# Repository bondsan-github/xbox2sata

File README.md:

Aim
===
- Create a IDE to SATA bridge PCB with pass-through socket for XBox DVD cable.
- !3d render[3d render](/Images/3d_render.png)

Motivation
==========
- Remove the need for a 80 wire IDE cable
- Use existing IDE cable for DVD drive

Completed
=========
- Unverified schematic of Startech IDE2SATA pcb
- Startech IDE2SATA layer scans and annotations in GIMP .xcf image format.

To do
=====
Measure components;
- L1

- Find suitable 3V3 and ground points to tap on XBox motherboards
- Measure available space inside XBox under DVD drive.
  - there is/are a radial capacaitor/s close to the IDE header
    - I would like to not make a hole in the PCB for matched IDE to IDE routing lengths
    - The capactor/s have enough leg legnth to pull up and lay flat

- Can xbox ide connection be directly connected to DVD connection?
  - Simular how a IDE cable does?
  - IDE cable does have CSEL tied hi or low depending on device?
- Can LED circuit be removed? Is it for HDD activity?
- CSEL cable selection can be fixed as DVD will always be device 0 (slave) and SATA device 1 (master)?
- What capacitors are required for power input from xbox motherboard?

Requirements
============
- Marvell 88SA8052 - NNC2 IC
  -  PATA/ATAPI to SATA bridge chip W/ATAPI, 3 GBps SATA
     -  64 pin
     -  package: PQFN50P900X900X90-65
  - 1V2 Voltage regulator for Marvel IC Vdd
  - 3V3 for Marvel Vddio 
  - 25Mhz crystal oscillator
  - CNFG0,1,2 setup
  - T0,1,2,3,4,5,6,7,8 setup
  - will require 3V3 and ground solder points from all six motherboard revisions
    - 1.0 , 1.1 , 1.2 , 1.3 , 1.4 , 1.6/b

- xbox motherboard IDE socket
- DVD drive IDE header
- SATA to HDD/SATA socket

Desirables
==========
- Marvell 88SA8052 datasheet
- Connect pcb directly to xbox ide header on motherboard.
- Use motherboard 3V3 reducing one power regulator.
- Use existing IDE cable from pcb to dvd drive.
  - Cut or roll second connector behind dvd drive.
- Use power from existing molex connector to HDD/SSD.
  
Software used
=============
- GIMP 2.99.18 development release
- KiCad Schematic Editor 8.0.1
- Proteus 8.15 SP1
  
Sources
=======
- https://www.psdevwiki.com/ps3/88SA8040-TBC1
- https://consolemods.org/wiki/Xbox:Versions
- https://www.ioi.com.tw/products/proddetail.aspx?CatID=101&HostID=2010&DeviceID=3002&ProdID=1010114
- https://en.wikipedia.org/wiki/Parallel_ATA
- https://www.startech.com/en-gb/hdd/ide2sat2

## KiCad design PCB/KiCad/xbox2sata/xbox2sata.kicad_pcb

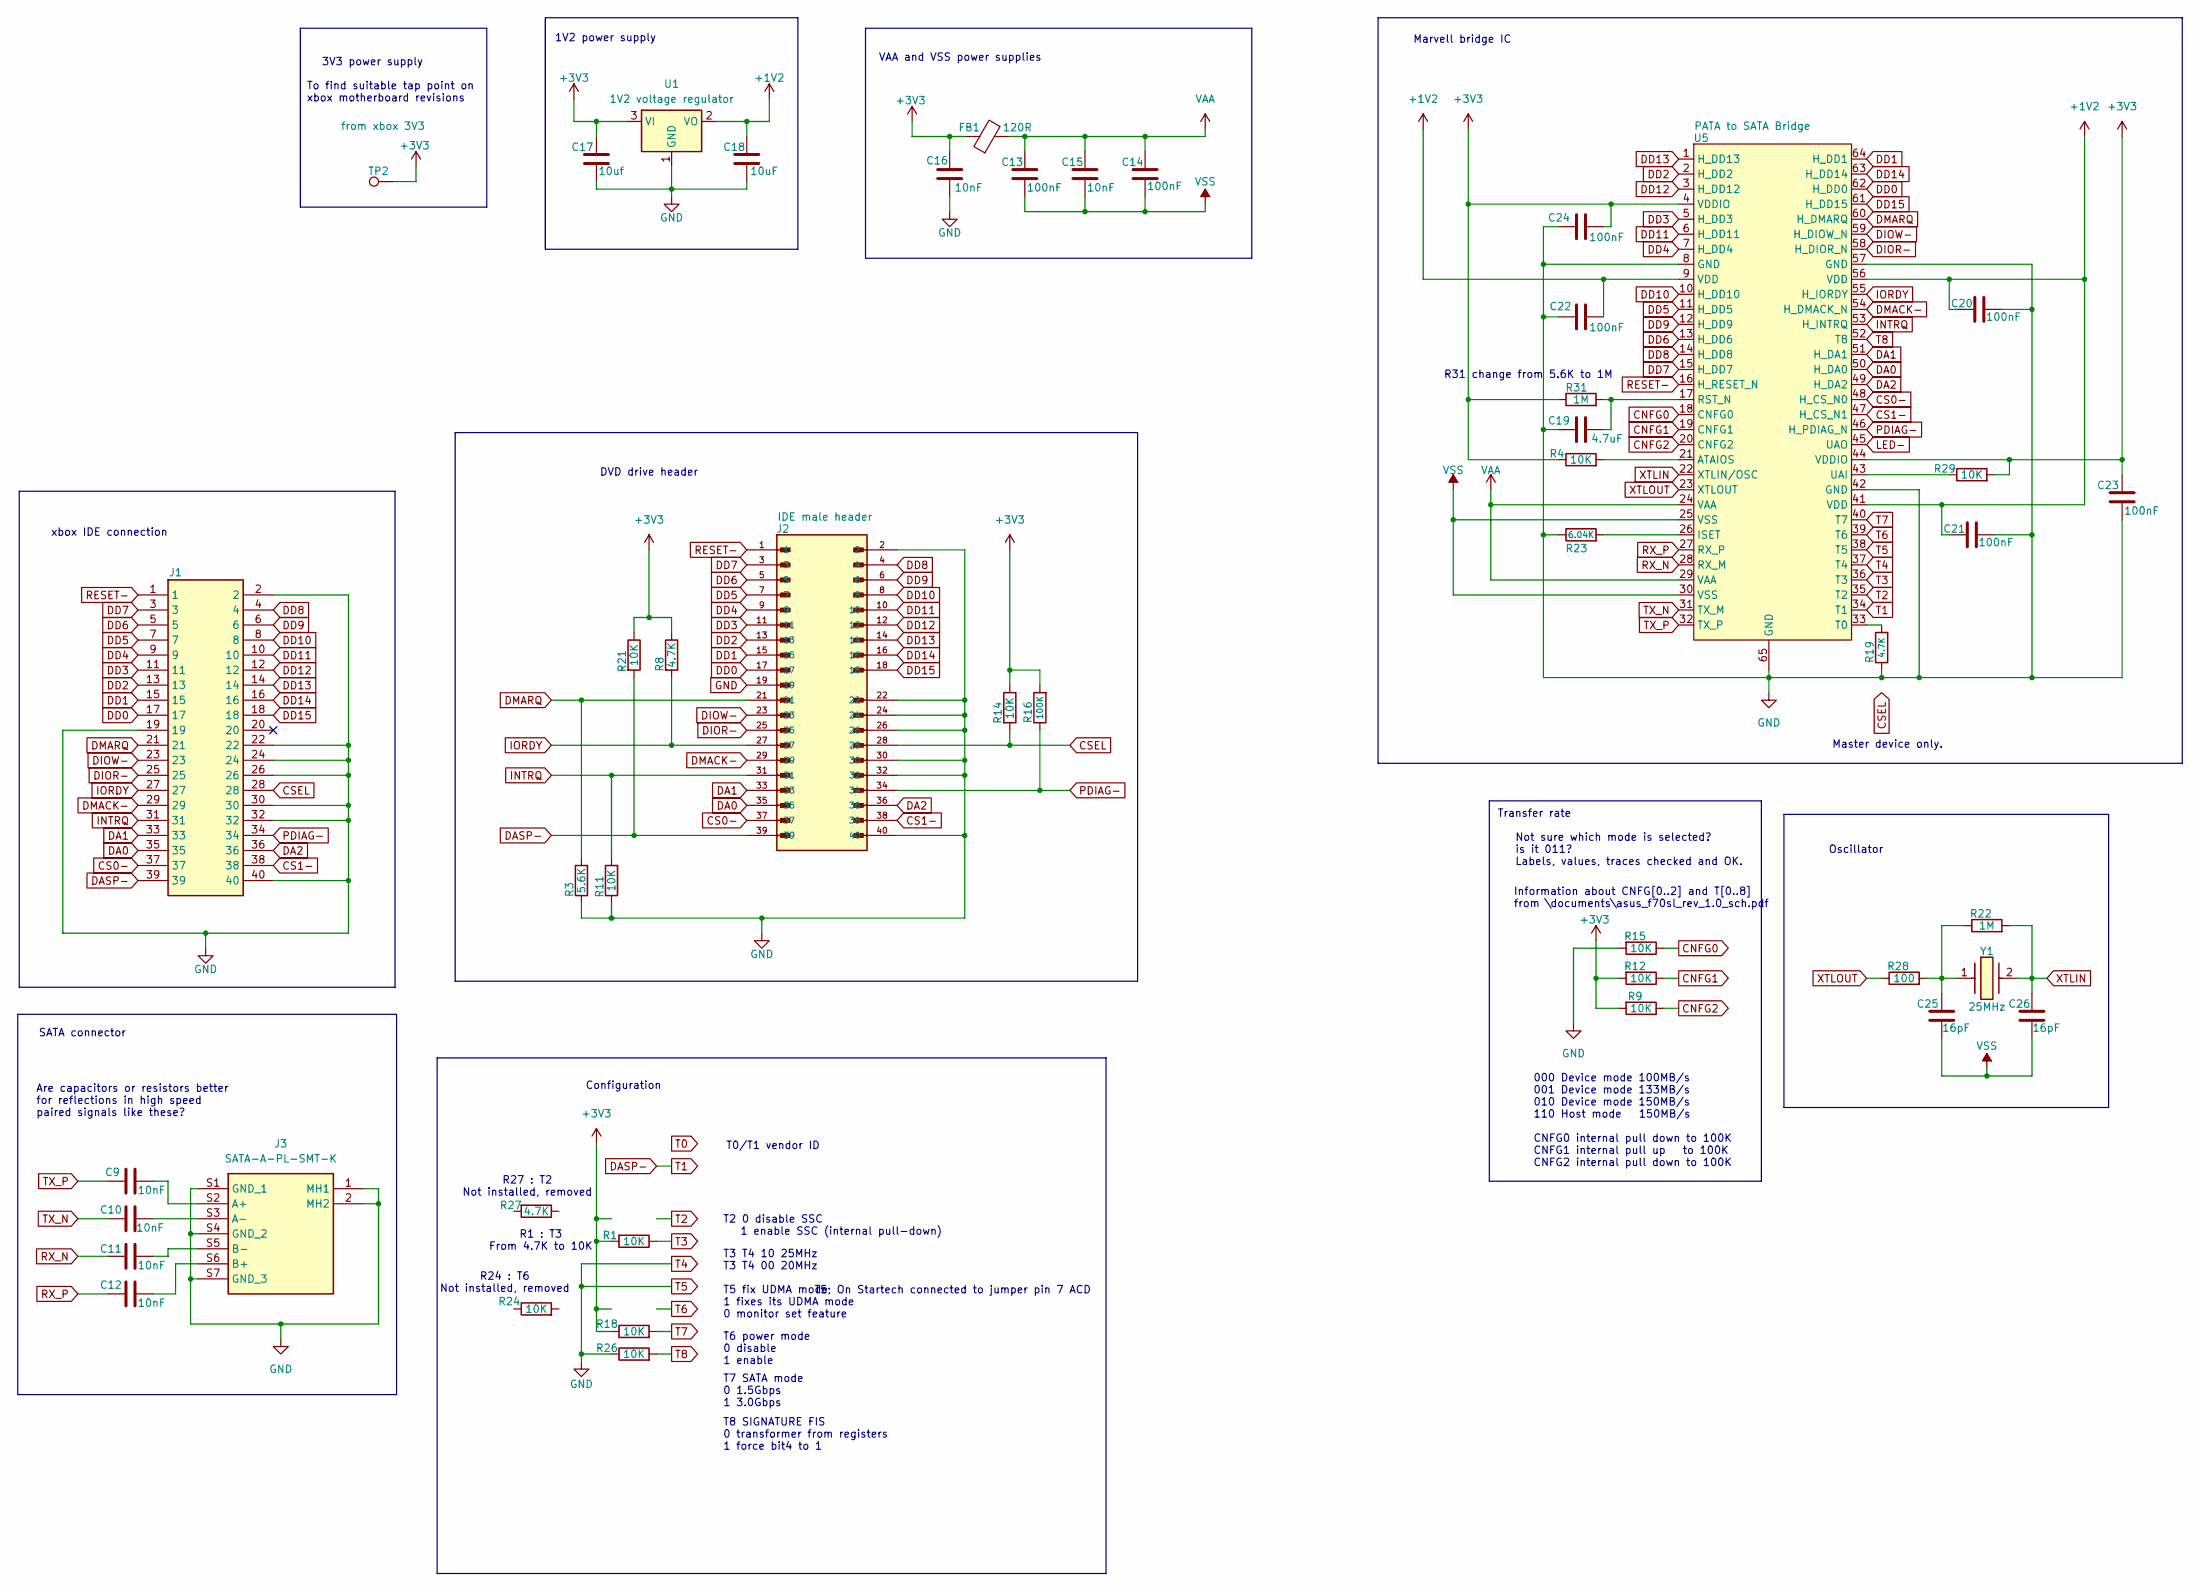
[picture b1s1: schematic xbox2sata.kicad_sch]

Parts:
C9, C10, C11, C12, C15, C16: 10nF; C_0402_1005Metric_Pad0.74x0.62mm_HandSolder
C13, C14, C20, C21, C22, C23, C24: 100nF; C_0402_1005Metric_Pad0.74x0.62mm_HandSolder
C17: 10uf; C_0805_2012Metric
C18: 10uF; C_0805_2012Metric
C19: 4.7uF; C_0402_1005Metric_Pad0.74x0.62mm_HandSolder
C25, C26: 16pF; C_0402_1005Metric_Pad0.74x0.62mm_HandSolder
FB1: 120R; L_0603_1608Metric; Current rating 2A
J1: 929975-01-20-RK; RHDR40W76P254_2X20_5080X508X826P; Mouser Part Number 517-929975-01-20-RK
J2: 61203921621; WURTH-ELEKTRONIK_61203921621; PARTREV 002.000
J3: SATA-A-PL-SMT-K; SATAAPLSMTK; Mouser Part Number 737-SATA-A-PL-SMT-K
R1, R4, R9, R11, R12, R14, R15, R18, R21, R24, R26, R29: 10K; R_0402_1005Metric_Pad0.72x0.64mm_HandSolder
R3: 5.6K; R_0402_1005Metric_Pad0.72x0.64mm_HandSolder
R8, R19, R27: 4.7K; R_0402_1005Metric_Pad0.72x0.64mm_HandSolder
R16: 100K; R_0402_1005Metric_Pad0.72x0.64mm_HandSolder
R22, R31: 1M; R_0402_1005Metric_Pad0.72x0.64mm_HandSolder
R23: 6.04K; R_0402_1005Metric_Pad0.72x0.64mm_HandSolder
R28: 100; R_0402_1005Metric_Pad0.72x0.64mm_HandSolder
TP2: from xbox 3V3; TestPoint_THTPad_2.5x2.5mm_Drill1.2mm
U1: 1V2 voltage regulator; SOT-89-3_Handsoldering
U5: 88SA8052; QFN-64-1EP_9x9mm_P0.5mm_EP3.4x3.4mm_ThermalVias
Y1: 25MHz; Crystal; Mouser Part Number 815-ABLS25MHZ16A4HFT

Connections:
+1V2: C18.1, C20.1, C21.1, C22.2, U1.2 (VO), U5.9 (VDD), U5.41 (VDD), U5.56 (VDD)
+3V3: C16.1, C17.2, C23.1, C24.2, FB1.1, R1.2, R4.1, R8.1, R9.2, R12.2, R14.1, R16.2, R18.1, R21.1, R29.2, R31.1, TP2.1, U1.3 (VI), U5.4 (VDDIO), U5.44 (VDDIO)
CNFG0: R15.1, U5.18 (CNFG0)
CNFG1: R12.1, U5.19 (CNFG1)
CNFG2: R9.1, U5.20 (CNFG2)
CS0-: J1.37, J2.37, U5.48 (H_CS_N0)
CS1-: J1.38, J2.38, U5.47 (H_CS_N1)
CSEL: J1.28, J2.28, R14.2
DA0: J1.35, J2.35, U5.50 (H_DA0)
DA1: J1.33, J2.33, U5.51 (H_DA1)
DA2: J1.36, J2.36, U5.49 (H_DA2)
DASP-: J1.39, J2.39, R21.2, U5.34 (T1)
DD0: J1.17, J2.17, U5.62 (H_DD0)
DD1: J1.15, J2.15, U5.64 (H_DD1)
DD2: J1.13, J2.13, U5.2 (H_DD2)
DD3: J1.11, J2.11, U5.5 (H_DD3)
DD4: J1.9, J2.9, U5.7 (H_DD4)
DD5: J1.7, J2.7, U5.11 (H_DD5)
DD6: J1.5, J2.5, U5.13 (H_DD6)
DD7: J1.3, J2.3, U5.15 (H_DD7)
DD8: J1.4, J2.4, U5.14 (H_DD8)
DD9: J1.6, J2.6, U5.12 (H_DD9)
DD10: J1.8, J2.8, U5.10 (H_DD10)
DD11: J1.10, J2.10, U5.6 (H_DD11)
DD12: J1.12, J2.12, U5.3 (H_DD12)
DD13: J1.14, J2.14, U5.1 (H_DD13)
DD14: J1.16, J2.16, U5.63 (H_DD14)
DD15: J1.18, J2.18, U5.61 (H_DD15)
DIOR-: J1.25, J2.25, U5.58 (H_DIOR_N)
DIOW-: J1.23, J2.23, U5.59 (H_DIOW_N)
DMACK-: J1.29, J2.29, U5.54 (H_DMACK_N)
DMARQ: J1.21, J2.21, R3.2, U5.60 (H_DMARQ)
GND: C16.2, C17.1, C18.2, C19.1, C20.2, C21.2, C22.1, C23.2, C24.1, J1.2, J1.19, J1.22, J1.24, J1.26, J1.30, J1.32, J1.40, J2.2, J2.19, J2.22, J2.24, J2.26, J2.30, J2.32, J2.40, J3.1 (MH1), J3.2 (MH2), J3.S1 (GND_1), J3.S4 (GND_2), J3.S7 (GND_3), R3.1, R11.1, R15.2, R19.1, R23.1, R26.1, U1.1 (GND), U5.8 (GND), U5.37 (T4), U5.38 (T5), U5.42 (GND), U5.57 (GND), U5.65 (GND)
INTRQ: J1.31, J2.31, R11.2, U5.53 (H_INTRQ)
IORDY: J1.27, J2.27, R8.2, U5.55 (H_IORDY)
LED-: U5.45 (UAO)
unnamed: C25.1, R22.1, R28.2, Y1.1
unnamed: C9.2, J3.S2 (A+)
unnamed: C10.2, J3.S3 (A-)
unnamed: C12.2, J3.S6 (B+)
unnamed: C11.2, J3.S5 (B-)
unnamed: R4.2, U5.21 (ATAIOS)
unnamed: R23.2, U5.26 (ISET)
unnamed: C19.2, R31.2, U5.17 (RST_N)
unnamed: R19.2, U5.33 (T0)
unnamed: R29.1, U5.43 (UAI)
PDIAG-: J1.34, J2.34, R16.1, U5.46 (H_PDIAG_N)
RESET-: J1.1, J2.1, U5.16 (H_RESET_N)
RX_N: C11.1, U5.28 (RX_M)
RX_P: C12.1, U5.27 (RX_P)
T2: U5.35 (T2)
T3: R1.1, U5.36 (T3)
T6: U5.39 (T6)
T7: R18.2, U5.40 (T7)
T8: R26.2, U5.52 (T8)
TX_N: C10.1, U5.31 (TX_M)
TX_P: C9.1, U5.32 (TX_P)
VAA: C13.1, C14.1, C15.1, FB1.2, U5.24 (VAA), U5.29 (VAA)
VSS: C13.2, C14.2, C15.2, C25.2, C26.2, U5.25 (VSS), U5.30 (VSS)
XTLIN: C26.1, R22.2, U5.22 (XTLIN/OSC), Y1.2
XTLOUT: R28.1, U5.23 (XTLOUT)

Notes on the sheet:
000 Device mode 100MB/s 001 Device mode 133MB/s 010 Device mode 150MB/s 110 Host mode 150MB/s CNFG0 internal pull down to 100K CNFG1 internal pull up to 100K CNFG2 internal pull down to 100K
VAA and VSS power supplies
xbox IDE connection
R24 : T6 Not installed, removed
T5 fix UDMA mode 1 fixes its UDMA mode 0 monitor set feature
Information about CNFG[0..2] and T[0..8] from \documents\asus_f70sl_rev_1.0_sch.pdf
R31 change from 5.6K to 1M
T3 T4 10 25MHz T3 T4 00 20MHz
Master device only.
DVD drive header
SATA connector
T5; On Startech connected to jumper pin 7 ACD
Configuration
T7 SATA mode 0 1.5Gbps 1 3.0Gbps
3V3 power supply
Marvell bridge IC
To find suitable tap point on xbox motherboard revisions
T6 power mode 0 disable 1 enable
1V2 power supply
Are capacitors or resistors better for reflections in high speed paired signals like these?
R1 : T3 From 4.7K to 10K
T0/T1 vendor ID
Oscillator
T2 0 disable SSC 1 enable SSC (internal pull-down)
Transfer rate
R27 : T2 Not installed, removed
T8 SIGNATURE FIS 0 transformer from registers 1 force bit4 to 1
Not sure which mode is selected? is it 011? Labels, values, traces checked and OK.

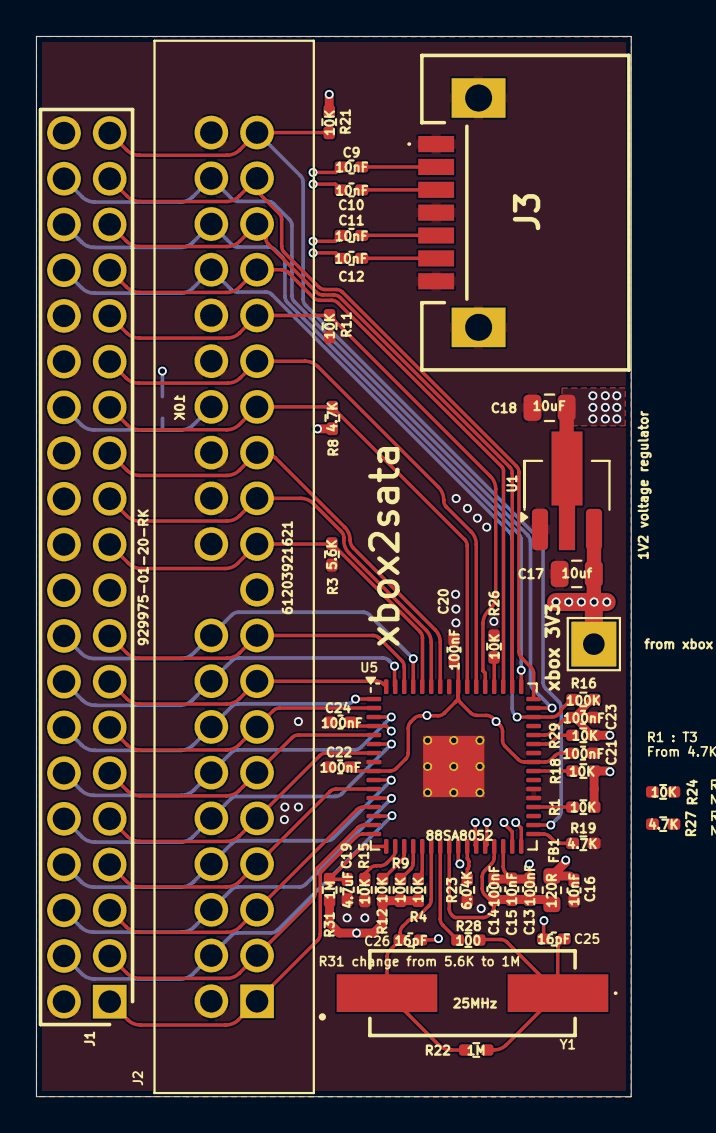
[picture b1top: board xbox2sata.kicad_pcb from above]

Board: 4 copper layers, 33.0 x 58.9 mm, 47 parts (1 on the bottom side), 58 nets.

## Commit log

2024-03-20 Update README.md
    added questions about what is required from Startech pcb to xbox pcb.
2024-03-20 additions to XBox to SATA proteus
2024-03-20 Images added
    Added v1.6 motherboard voltage readings image.
    Added screenshot of xbox2sata 3d layout.
2024-03-21 additions to xbox2sata proteus schematic
2024-03-21 Created KiCad project with 88SA symbol
    new KiCad project xbox2sata with Marvel 88SA symbol
2024-03-21 KIiCad symbols and footprints added
    Added symbols, footprints, 3d models for Marvel 88SA, SATA data socket and IDE socket for DVD drive cable.
    To try another 3d model for IDE socket.
2024-03-22 KiCad updates
    Crystal resonator added, 3d model for ide header fixed.
2024-03-22 PCB folder structure
    Created two sub folders in PCB; Proteus and KiCad and moved respective files into folders.
2024-03-24 KiCad updates
    Nets and some components added
2024-03-25 KiCad update
    Added to schematic and pcb
2024-03-27 Notes added to KiCad schematic
    Requests for checking routing and signals are correct.
2024-04-01 ground cable point removed
    ground to xbox through ide header
2024-06-26 slight changes to schematic
2024-06-27 1V2 regulator circuit corrected, all labels need correcting
    1V2 regulator circuit corrected, all labels need correcting
2024-06-28 T0-8 updated, label changes
    Several cap and res labels changed, T0-8 config changed, layers.xcf saved with compression.
2024-07-01 oscillator circuit corrected
2024-07-03 Variable voltage regulator changed to fixed 1V2
    Variable voltage regulator changed to fixed 1V2 regulator. L1 is a ferrite bead not a inductor.
2024-07-08 IDE pins changes
    IDE pins 32 and 34 on xbox only connect to test points. Therefore connected to ground.
2024-07-11 bill of matierals
    spreadsheet for bill of materials,
    IDE female socket changed to cheaper option,
    SATA socket changed to right angle, recommend by doofus.
2024-07-16 reset and csel correct circuit from startech
    10K resistor (R14) pull-up to 3V3 added to CSEL IDE pin 28
    4.7K resistor (R19) pull-down to ground on T0 U5 pin 33 to device as IDE master
    positive power supply icons changed from Global labels to power symbols
2024-07-19 Reset-Negative was not enabled
    10K resistor (R14) pull-up to 3V3 added to CSEL IDE pin 28
    4.7K resistor (R19) pull-down to ground on T0 U5 pin 33 to device as IDE master
    Positive power supply icons changed from Global labels to Power symbols
    Via sizes changed to 0.3 and 0.5 mm for jlcpcb requirements
    Bill of materials updated
    Mouser shared basket created;
2024-08-01 Two resistors removed, two component values changed
    R27 : T2
    Not installed, removed
    R1 : T3
    From 4.7K to 10K
    R24 : T6
    Not installed, removed
2024-08-25 why u not work!?!
    going back from start checking for errors, but I'm guessing the error lies with the IDE pull-up and down resistors and possibly the T0-8 configuration setup.
2024-08-25 file rename
    changed space to an underscore
